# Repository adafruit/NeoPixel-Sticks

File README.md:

# NeoPixel Stick

__Format is EagleCAD schematic and board layout__

<a href="http://www.adafruit.com/products/1426"><br/>5050 RGB LEDs. Click here to purchase one from the Adafruit shop</a>
<br><br>
<a href="http://www.adafruit.com/products/6509"><br/>5050 WWA White LEDs. Click here to purchase one from the Adafruit shop</a>

Make your own little LED strip arrangement with this stick of NeoPixel LEDs. We crammed 8 of the tiny 5050 (5mm x 5mm) smart RGB LEDs onto a PCB with mounting holes and a chainable design. Use only one microcontroller pin to control as many as you can chain together! Each LED is addressable as the driver chip is inside the LED. Each one has ~18mA constant current drive so the color will be very consistent even if the voltage varies, and no external choke resistors are required making the design slim. Power the whole thing with 5VDC (4-7V works) and you're ready to rock.

The LEDs are 'chainable' by connecting the output of one stick into the input of another - see the photo above. There is a single data line with a very timing-specific protocol. Since the protocol is very sensitive to timing, it requires a real-time microconroller such as an AVR, Arduino, PIC, mbed, etc. It cannot be used with a Linux-based microcomputer or interpreted microcontroller such as the netduino or Basic Stamp. Our wonderfully-written [Neopixel library for Arduino supports these pixels!](https://github.com/adafruit/Adafruit_NeoPixel) As it requires hand-tuned assembly it is only for AVR cores but others may have ported this chip driver code so please google around. An 8MHz or faster processor is required.

Comes as a single stick with 8 individually addressable RGB LEDs OR WWA LEDs, which are addressable white LEDs with three addressable tints/color temperatures assembled and tested.

[Our detailed NeoPixel Uberguide has everything you need to use NeoPixels in any shape and size. Including ready-to-go library & example code for the Arduino UNO/Duemilanove/Diecimila, Flora/Micro/Leonardo, Trinket/Gemma, Arduino Due & Arduino Mega/ADK (all versions)](http://learn.adafruit.com/adafruit-neopixel-uberguide)

## License

Adafruit invests time and resources providing this open source design, 
please support Adafruit and open-source hardware by purchasing 
products from Adafruit!

Designed by Adafruit Industries.  
Creative Commons Attribution, Share-Alike license, check license.txt for more information
All text above must be included in any redistribution

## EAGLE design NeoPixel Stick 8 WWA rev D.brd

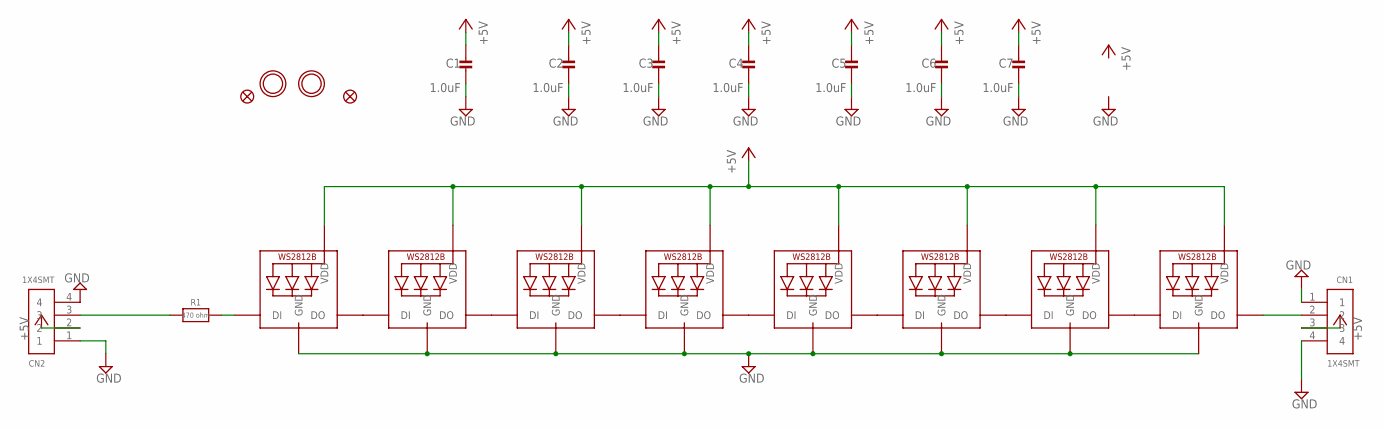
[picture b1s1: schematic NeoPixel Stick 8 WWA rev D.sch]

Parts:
C1, C2, C3, C4, C5, C6, C7: 1.0uF; 0603-NO
CN1, CN2: 1X4SMT; 1X4-SMT
FID1, FID3: FIDUCIAL_1MM
LED1, LED2, LED3, LED4, LED5, LED6, LED7, LED8: SKC6812; WS2812B-NARROW
R1: 470 ohm; 0603-NO
U$2, U$3: MOUNTINGHOLE2.0; MOUNTINGHOLE_2.0_PLATED

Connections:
+5V: C1.1, C2.1, C3.1, C4.1, C5.1, C6.1, C7.1, CN1.3, CN2.2, LED1.1-VDD (VDD), LED2.1-VDD (VDD), LED3.1-VDD (VDD), LED4.1-VDD (VDD), LED5.1-VDD (VDD), LED6.1-VDD (VDD), LED7.1-VDD (VDD), LED8.1-VDD (VDD)
GND: C1.2, C2.2, C3.2, C4.2, C5.2, C6.2, C7.2, CN1.1, CN1.4, CN2.1, CN2.4, LED1.3-GND (GND), LED2.3-GND (GND), LED3.3-GND (GND), LED4.3-GND (GND), LED5.3-GND (GND), LED6.3-GND (GND), LED7.3-GND (GND), LED8.3-GND (GND)
unnamed: LED1.2-DOUT (DO), LED2.4-DIN (DI)
unnamed: LED2.2-DOUT (DO), LED3.4-DIN (DI)
unnamed: LED3.2-DOUT (DO), LED4.4-DIN (DI)
unnamed: LED4.2-DOUT (DO), LED5.4-DIN (DI)
unnamed: LED5.2-DOUT (DO), LED6.4-DIN (DI)
unnamed: LED6.2-DOUT (DO), LED7.4-DIN (DI)
unnamed: LED7.2-DOUT (DO), LED8.4-DIN (DI)
unnamed: CN2.3, R1.1
unnamed: CN1.2, LED8.2-DOUT (DO)
unnamed: LED1.4-DIN (DI), R1.2

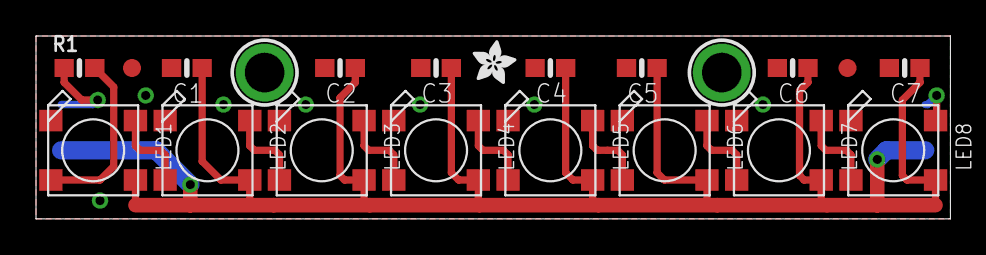
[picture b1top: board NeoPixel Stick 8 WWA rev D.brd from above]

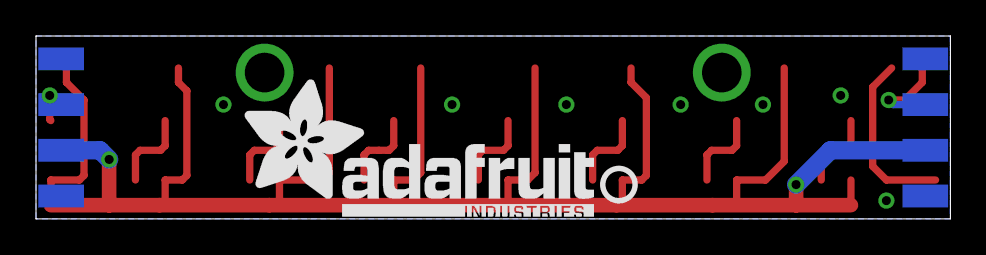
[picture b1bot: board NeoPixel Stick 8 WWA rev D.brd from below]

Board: 2 copper layers, 50.8 x 10.2 mm, 35 parts (14 on the bottom side), 12 nets.

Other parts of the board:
PLABEL0: PLABEL0
PLABEL1: PLABEL1
PLABEL2: PLABEL2
PLABEL3: PLABEL3
PLABEL4: PLABEL4
PLABEL5: PLABEL5
PLABEL6: PLABEL6
PLABEL7: PLABEL7
PLABEL8: PLABEL8
PLABEL9: PLABEL9
U$1: ADAFRUIT_TEXT_20MM
U$4: ADAFRUIT_2.5MM
U$5: PCBFEAT-REV-040

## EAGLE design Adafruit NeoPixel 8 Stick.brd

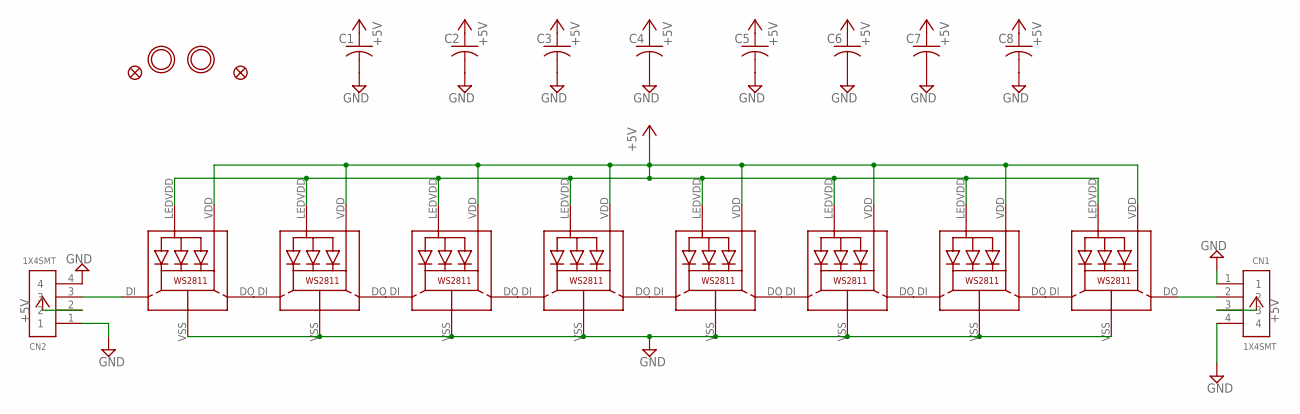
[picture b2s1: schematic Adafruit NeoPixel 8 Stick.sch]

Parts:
C1, C2, C3, C4, C5, C6, C7, C8: C-USC0805K; C0805K
CN1, CN2: 1X4SMT; 1X4-SMT
FID1, FID3: FIDUCIAL""; FIDUCIAL_1MM
LED1, LED2, LED3, LED4, LED5, LED6, LED7, LED8: WS28115050
U$2, U$3: MOUNTINGHOLE2.0; MOUNTINGHOLE_2.0_PLATED

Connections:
+5V: C1.1, C2.1, C3.1, C4.1, C5.1, C6.1, C7.1, C8.1, CN1.3, CN2.2, LED1.LEDVDD, LED1.VDD, LED2.LEDVDD, LED2.VDD, LED3.LEDVDD, LED3.VDD, LED4.LEDVDD, LED4.VDD, LED5.LEDVDD, LED5.VDD, LED6.LEDVDD, LED6.VDD, LED7.LEDVDD, LED7.VDD, LED8.LEDVDD, LED8.VDD
GND: C1.2, C2.2, C3.2, C4.2, C5.2, C6.2, C7.2, C8.2, CN1.1, CN1.4, CN2.1, CN2.4, LED1.VSS (GND), LED2.VSS (GND), LED3.VSS (GND), LED4.VSS (GND), LED5.VSS (GND), LED6.VSS (GND), LED7.VSS (GND), LED8.VSS (GND)
unnamed: LED1.DO, LED2.DI
unnamed: LED2.DO, LED3.DI
unnamed: LED3.DO, LED4.DI
unnamed: LED4.DO, LED5.DI
unnamed: LED5.DO, LED6.DI
unnamed: LED6.DO, LED7.DI
unnamed: LED7.DO, LED8.DI
unnamed: CN2.3, LED1.DI
unnamed: CN1.2, LED8.DO

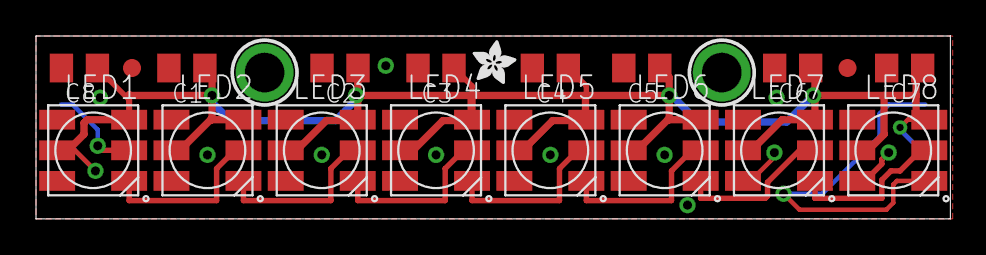
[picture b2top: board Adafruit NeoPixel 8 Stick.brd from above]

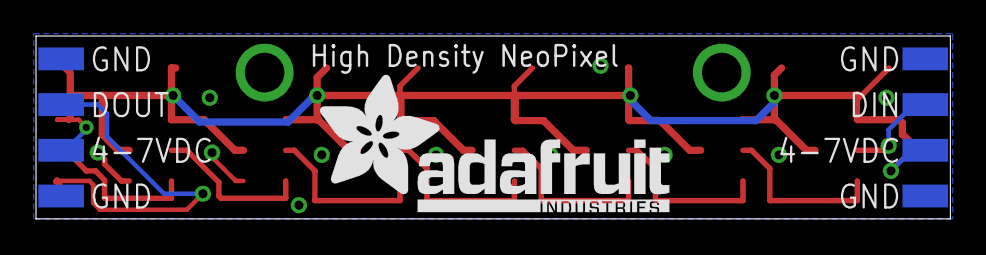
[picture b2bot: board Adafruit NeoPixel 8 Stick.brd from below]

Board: 2 copper layers, 50.8 x 10.2 mm, 24 parts (3 on the bottom side), 11 nets.

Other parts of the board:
U$1: ADAFRUIT_TEXT_20MM
U$4: ADAFRUIT_2.5MM

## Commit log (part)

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2013-12-17 init
2015-06-26 4-pin version!
2019-06-14 readme + image
2019-06-14 added missing license

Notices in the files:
parts and their libraries:
microbuilder: This work is placed in the public domain, and may be freely used for commercial and non-commercial work with the following conditions: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
